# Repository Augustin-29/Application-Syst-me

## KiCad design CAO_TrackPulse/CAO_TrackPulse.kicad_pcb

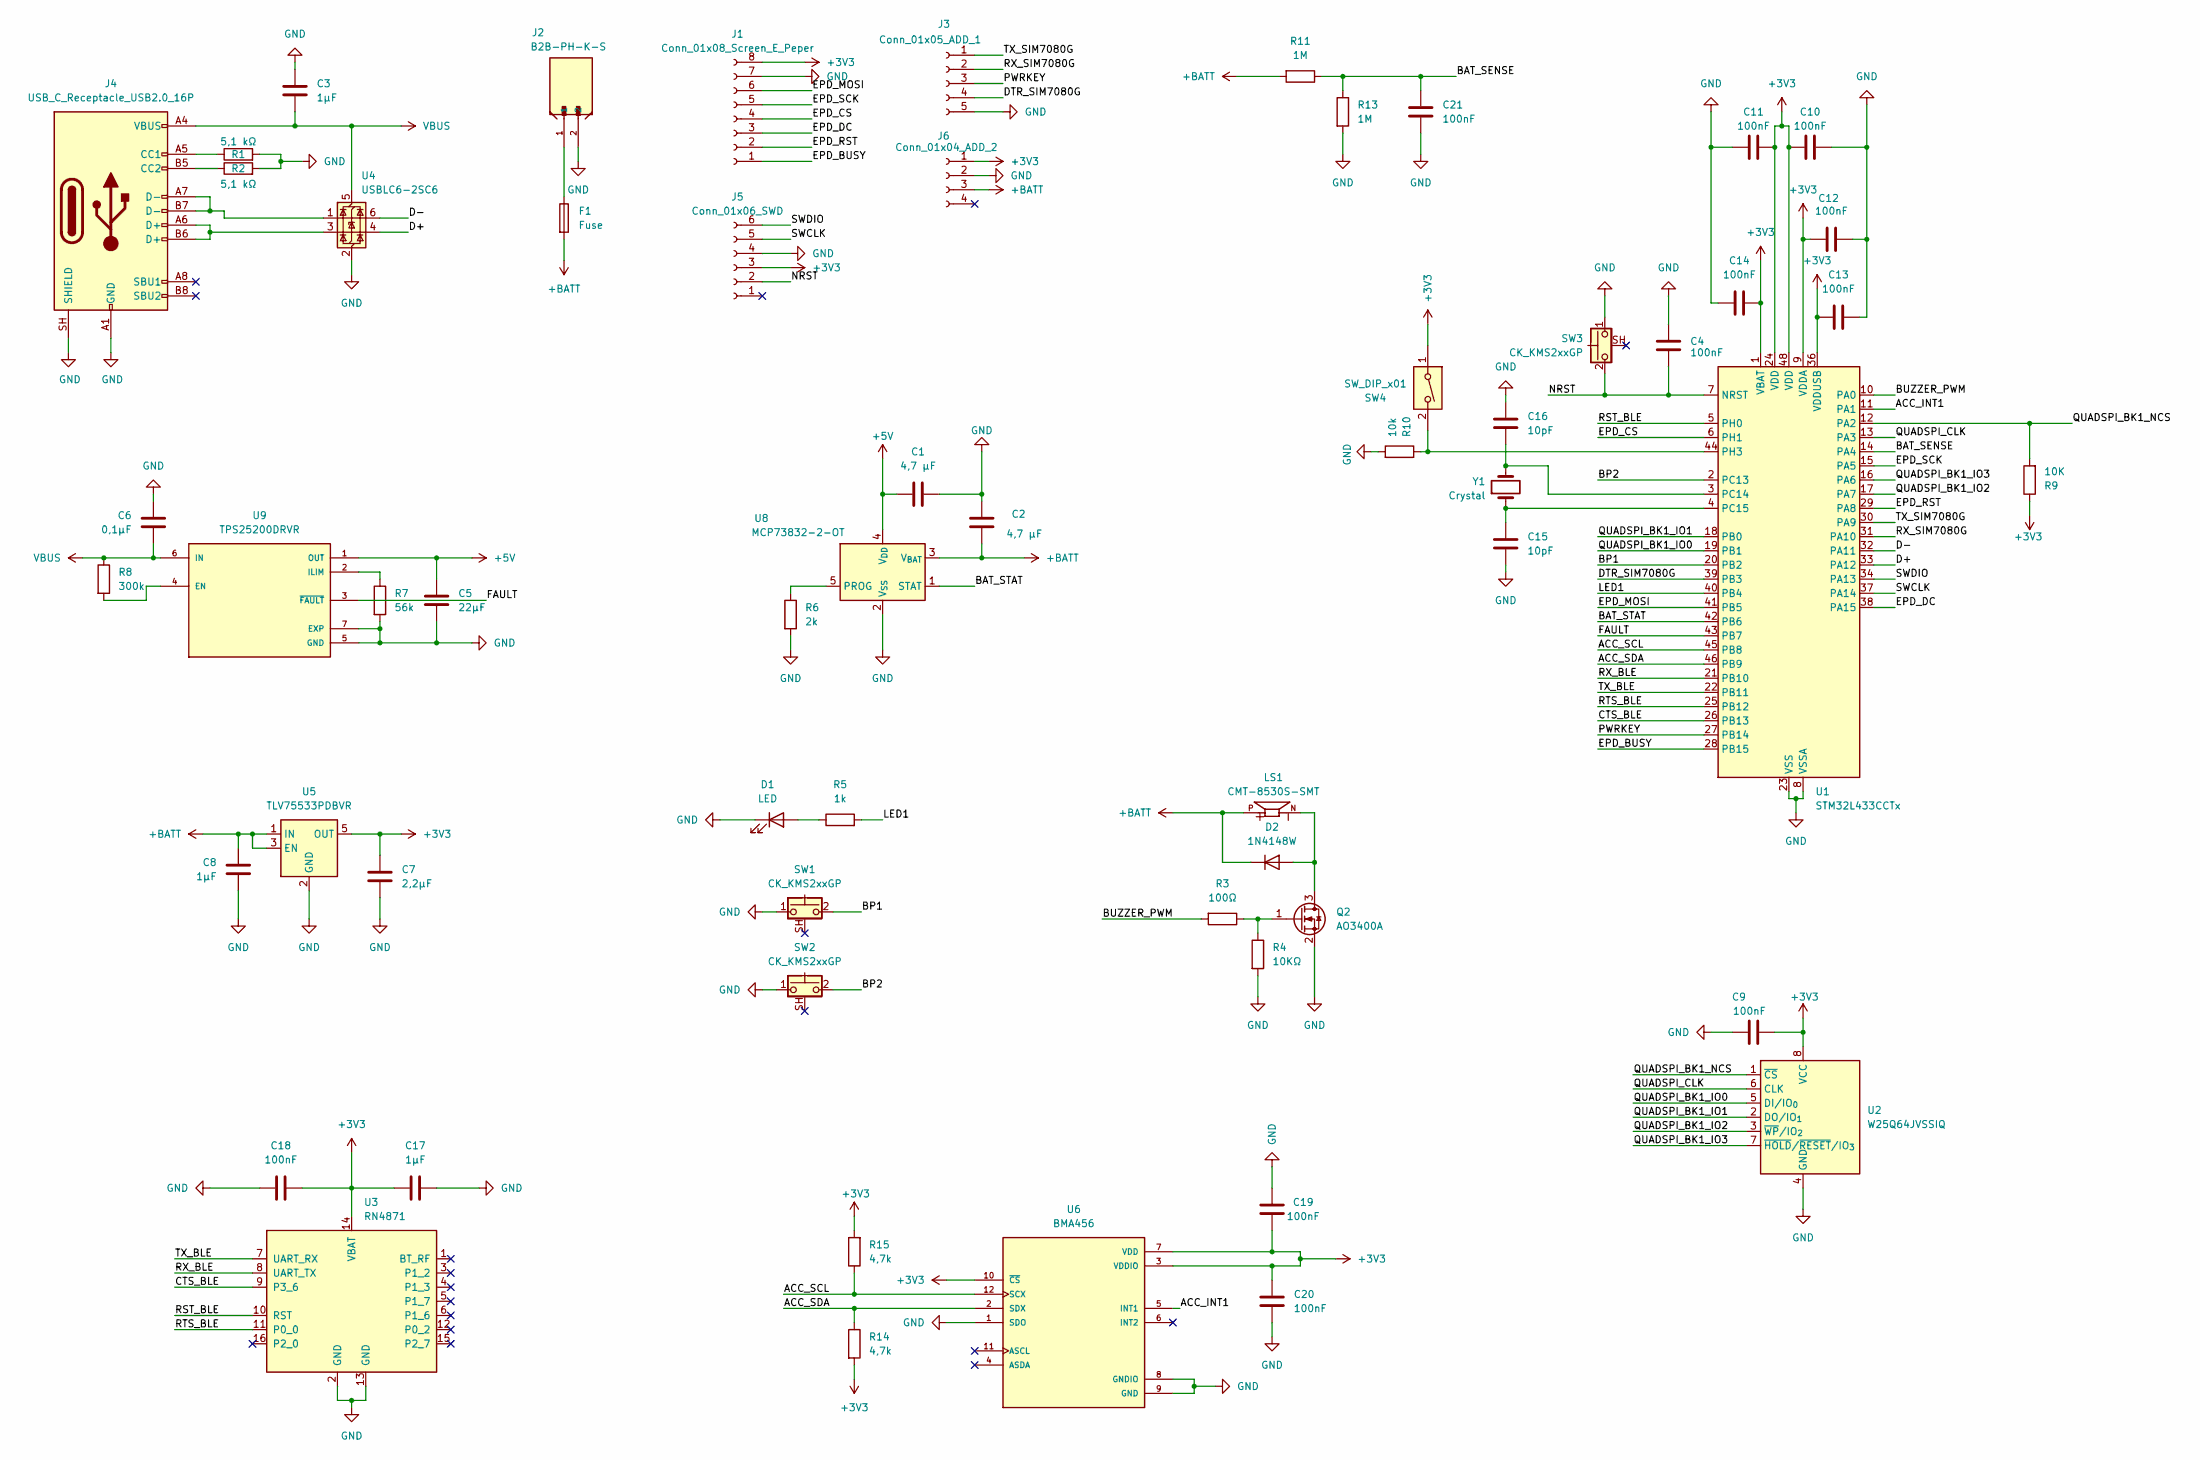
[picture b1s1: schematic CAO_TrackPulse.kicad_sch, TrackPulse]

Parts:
C1, C2: 4,7 µF; C_0805_2012Metric_Pad1.18x1.45mm_HandSolder
C3, C8, C17: 1µF; C_0805_2012Metric_Pad1.18x1.45mm_HandSolder
C4, C9, C10, C11, C12, C13, C14, C18, C19, C20, C21: 100nF; C_0805_2012Metric_Pad1.18x1.45mm_HandSolder
C5: 22µF; C_0805_2012Metric_Pad1.18x1.45mm_HandSolder
C6: 0,1µF; C_0805_2012Metric_Pad1.18x1.45mm_HandSolder
C7: 2,2µF; C_0805_2012Metric_Pad1.18x1.45mm_HandSolder
C15, C16: 10pF; C_0805_2012Metric_Pad1.18x1.45mm_HandSolder
D1: LED; LED_0805_2012Metric_Pad1.15x1.40mm_HandSolder
D2: 1N4148W; D_SOD-123
F1: Fuse; Fuse_0805_2012Metric_Pad1.15x1.40mm_HandSolder
J1: Conn_01x08_Screen_E_Peper; PinHeader_1x08_P2.54mm_Vertical
J2: B2B-PH-K-S; JST_B2B-PH-K-S
J3: Conn_01x05_ADD_1; PinHeader_1x05_P2.54mm_Vertical
J4: USB_C_Receptacle_USB2.0_16P; USB_C_Receptacle_HRO_TYPE-C-31-M-12
J5: Conn_01x06_SWD; Tag-Connect_TC2030-IDC-NL_2x03_P1.27mm_Vertical
J6: Conn_01x04_ADD_2; PinHeader_1x04_P2.54mm_Vertical
LS1: CMT-8530S-SMT; MagneticBuzzer_CUI_CMT-8504
Q2: AO3400A; SOT-23
R1, R2: 5,1 kΩ; C_0805_2012Metric_Pad1.18x1.45mm_HandSolder
R3: 100Ω; C_0805_2012Metric_Pad1.18x1.45mm_HandSolder
R4: 10KΩ; C_0805_2012Metric_Pad1.18x1.45mm_HandSolder
R5: 1k; C_0805_2012Metric_Pad1.18x1.45mm_HandSolder
R6: 2k; C_0805_2012Metric_Pad1.18x1.45mm_HandSolder
R7: 56k; C_0805_2012Metric_Pad1.18x1.45mm_HandSolder
R8: 300k; C_0805_2012Metric_Pad1.18x1.45mm_HandSolder
R9: 10K; C_0805_2012Metric_Pad1.18x1.45mm_HandSolder
R10: 10k; C_0805_2012Metric_Pad1.18x1.45mm_HandSolder
R11, R13: 1M; C_0805_2012Metric_Pad1.18x1.45mm_HandSolder
R14, R15: 4,7k; C_0805_2012Metric_Pad1.18x1.45mm_HandSolder
SW1, SW2, SW3: CK_KMS2xxGP; SW_SPST_CK_KMS2xxGP
SW4: SW_DIP_x01; SW_DIP_SPSTx01_Slide_Omron_A6S-110x_W8.9mm_P2.54mm
U1: STM32L433CCTx; LQFP-48_7x7mm_P0.5mm
U2: W25Q64JVSSIQ; SOIC-8_5.3x5.3mm_P1.27mm
U3: RN4871; Microchip_RN4871
U4: USBLC6-2SC6; SOT-23-6
U5: TLV75533PDBVR; SOT-23-5
U6: BMA456; LGA-12_2x2mm_P0.5mm; MPN BMA456
U8: MCP73832-2-OT; SOT-23-5
U9: TPS25200DRVR; WSON-6-1EP_2x2mm_P0.65mm_EP1x1.6mm; PARTREV D
Y1: Crystal; Crystal_SMD_3215-2Pin_3.2x1.5mm

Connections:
+3V3: C7.1, C9.2, C10.1, C11.1, C12.1, C13.1, C14.2, C17.1, C18.2, C19.1, C20.1, J1.8, J5.3, J6.1, R9.1, R14.2, R15.2, SW4.1, U1.1 (VBAT), U1.9 (VDDA), U1.24 (VDD), U1.36 (VDDUSB), U1.48 (VDD), U2.8 (VCC), U3.14 (VBAT), U5.5 (OUT), U6.3 (VDDIO), U6.7 (VDD), U6.10 (~CS)
+5V: C1.2, C5.1, U8.4 (V_{DD}), U9.1 (OUT)
+BATT: C2.1, C8.2, D2.1 (K), F1.2, J6.3, LS1.P, R11.2, U5.1 (IN), U5.3 (EN), U8.3 (V_{BAT})
/ACC_INT1: U1.11 (PA1), U6.5 (INT1)
/ACC_SCL: R15.1, U1.45 (PB8), U6.12 (SCX)
/ACC_SDA: R14.1, U1.46 (PB9), U6.2 (SDX)
/BAT_SENSE: C21.1, R11.1, R13.1, U1.14 (PA4)
/BAT_STAT: U1.42 (PB6), U8.1 (STAT)
/BP1: SW1.2, U1.20 (PB2)
/BP2: SW2.2, U1.2 (PC13)
/BUZZER_PWM: R3.2, U1.10 (PA0)
/CTS_BLE: U1.26 (PB13), U3.9 (P3_6)
/D+: U1.33 (PA12), U4.4 (I/O2)
/D-: U1.32 (PA11), U4.6 (I/O1)
/DTR_SIM7080G: J3.4, U1.39 (PB3)
/EPD_BUSY: J1.1, U1.28 (PB15)
/EPD_CS: J1.4, U1.6 (PH1)
/EPD_DC: J1.3, U1.38 (PA15)
/EPD_MOSI: J1.6, U1.41 (PB5)
/EPD_RST: J1.2, U1.29 (PA8)
/EPD_SCK: J1.5, U1.15 (PA5)
/FAULT: U1.43 (PB7), U9.3 (~FAULT)
/LED1: R5.2, U1.40 (PB4)
/NRST: C4.2, J5.2, SW3.2, U1.7 (NRST)
/PWRKEY: J3.3, U1.27 (PB14)
/QUADSPI_BK1_IO0: U1.19 (PB1), U2.5 (DI/IO_{0})
/QUADSPI_BK1_IO1: U1.18 (PB0), U2.2 (DO/IO_{1})
/QUADSPI_BK1_IO2: U1.17 (PA7), U2.3 (~WP/IO_{2})
/QUADSPI_BK1_IO3: U1.16 (PA6), U2.7 (~HOLD/~RESET/IO_{3})
/QUADSPI_BK1_NCS: R9.2, U1.12 (PA2), U2.1 (~CS)
/QUADSPI_CLK: U1.13 (PA3), U2.6 (CLK)
/RST_BLE: U1.5 (PH0), U3.10 (RST)
/RTS_BLE: U1.25 (PB12), U3.11 (P0_0)
/RX_BLE: U1.21 (PB10), U3.8 (UART_TX)
/RX_SIM7080G: J3.2, U1.31 (PA10)
/SWCLK: J5.5, U1.37 (PA14)
/SWDIO: J5.6, U1.34 (PA13)
/TX_BLE: U1.22 (PB11), U3.7 (UART_RX)
/TX_SIM7080G: J3.1, U1.30 (PA9)
GND: C1.1, C2.2, C3.1, C4.1, C5.2, C6.1, C7.2, C8.1, C9.1, C10.2, C11.2, C12.2, C13.2, C14.1, C15.2, C16.1, C17.2, C18.1, C19.2, C20.2, C21.2, D1.1 (K), J1.7, J2.2, J3.5, J4.A1 (GND), J4.A12 (GND), J4.B1 (GND), J4.B12 (GND), J4.SH (SHIELD), J5.4, J6.2, Q2.2 (S), R1.2, R2.2, R4.2, R6.2, R7.2, R10.2, R13.2, SW1.1, SW2.1, SW3.1, U1.8 (VSSA), U1.23 (VSS), U1.35 (VSS), U1.47 (VSS), U2.4 (GND), U3.2 (GND), U3.13 (GND), U4.2 (GND), U5.2 (GND), U6.1 (SDO), U6.8 (GNDIO), U6.9 (GND), U8.2 (V_{SS}), U9.5 (GND), U9.7 (EXP)
unnamed: D1.2 (A), R5.1
unnamed: D2.2 (A), LS1.N, Q2.3 (D)
unnamed: F1.1, J2.1
unnamed: J4.A5 (CC1), R1.1
unnamed: J4.B5 (CC2), R2.1
unnamed: J4.A6 (D+), J4.B6 (D+), U4.3 (I/O2)
unnamed: J4.A7 (D-), J4.B7 (D-), U4.1 (I/O1)
unnamed: Q2.1 (G), R3.1, R4.1
unnamed: C16.2, U1.3 (PC14), Y1.2
unnamed: C15.1, U1.4 (PC15), Y1.1
unnamed: R10.1, SW4.2, U1.44 (PH3)
unnamed: R6.1, U8.5 (PROG)
unnamed: R8.2, U9.4 (EN)
unnamed: R7.1, U9.2 (ILIM)
VBUS: C3.2, C6.2, J4.A4 (VBUS), J4.A9 (VBUS), J4.B4 (VBUS), J4.B9 (VBUS), R8.1, U4.5 (VBUS), U9.6 (IN)

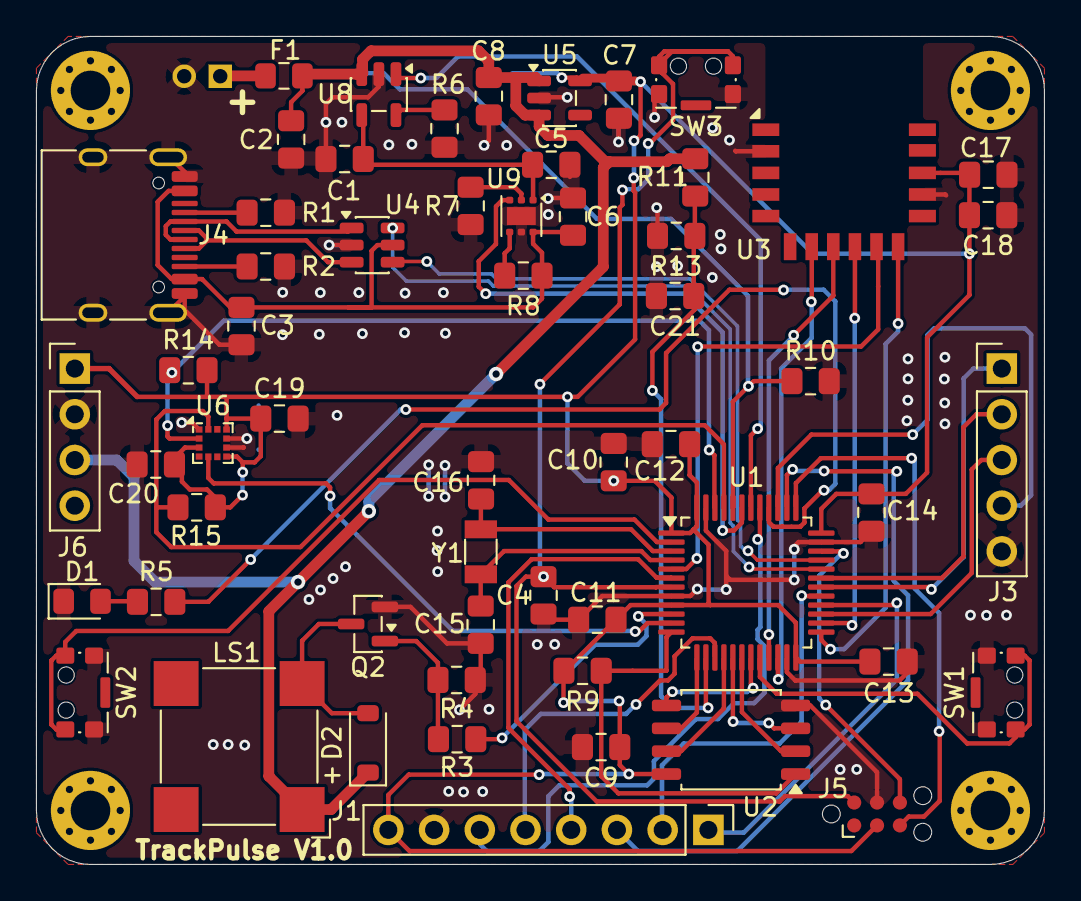
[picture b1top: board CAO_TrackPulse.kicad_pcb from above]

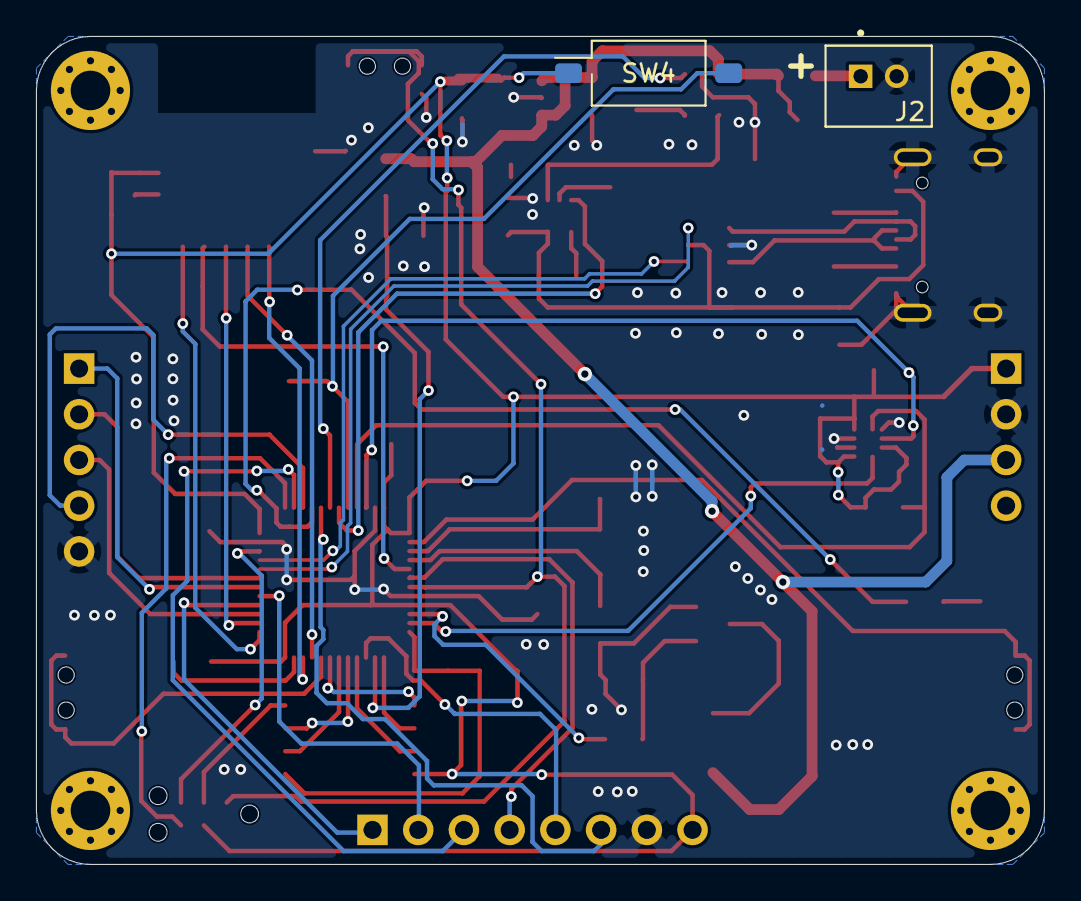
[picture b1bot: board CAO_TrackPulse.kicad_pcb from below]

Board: 2 copper layers, 56.0 x 46.0 mm, 59 parts (2 on the bottom side), 55 nets.

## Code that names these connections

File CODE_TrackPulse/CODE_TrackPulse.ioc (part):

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Mcu.Name=STM32L433C(B-C)Tx
Mcu.Package=LQFP48
Mcu.UserName=STM32L433CCTx
PA0.Signal=S_TIM2_CH1
PA1.GPIOParameters=GPIO_Label
PA1.GPIO_Label=ACC_INT1
PA1.Signal=GPXTI1
PA10.Mode=Asynchronous
PA10.Signal=USART1_RX
PA11.Mode=Device
PA11.Signal=USB_DM
PA12.Mode=Device
PA12.Signal=USB_DP
PA13\ (JTMS-SWDIO).Mode=Serial_Wire
PA13\ (JTMS-SWDIO).Signal=SYS_JTMS-SWDIO
PA14\ (JTCK-SWCLK).Mode=Serial_Wire
PA14\ (JTCK-SWCLK).Signal=SYS_JTCK-SWCLK
PA15\ (JTDI).GPIOParameters=GPIO_Label
PA15\ (JTDI).GPIO_Label=EPD_DC
PA15\ (JTDI).Signal=GPIO_Output
PA2.Mode=Single Bank 1
PA2.Signal=QUADSPI_BK1_NCS
PA3.Mode=Single Bank 1
PA3.Signal=QUADSPI_CLK
PA4.GPIOParameters=GPIO_Label
PA4.GPIO_Label=BAT_SENSE
PA4.Signal=ADCx_IN9
PA5.Mode=TX_Only_Simplex_Unidirect_Master
PA5.Signal=SPI1_SCK
PA6.Mode=Single Bank 1
PA6.Signal=QUADSPI_BK1_IO3
PA7.Mode=Single Bank 1
PA7.Signal=QUADSPI_BK1_IO2
PA8.GPIOParameters=PinState,GPIO_Label
PA8.GPIO_Label=EPD_RST
PA8.PinState=GPIO_PIN_SET
PA8.Signal=GPIO_Output
PA9.Mode=Asynchronous
PA9.Signal=USART1_TX
PB0.Mode=Single Bank 1
PB0.Signal=QUADSPI_BK1_IO1
PB1.Mode=Single Bank 1
PB1.Signal=QUADSPI_BK1_IO0
PB10.Mode=Asynchronous
PB10.Signal=LPUART1_RX
PB11.Mode=Asynchronous
PB11.Signal=LPUART1_TX
PB12.Mode=CTS_RTS
PB12.Signal=LPUART1_RTS
PB13.Mode=CTS_RTS
PB13.Signal=LPUART1_CTS
PB14.GPIOParameters=GPIO_Label
PB14.GPIO_Label=PWRKEY
PB14.Signal=GPIO_Output
PB15.GPIOParameters=GPIO_Label
PB15.GPIO_Label=EPD_BUSY
PB15.Signal=GPIO_Input
PB2.GPIOParameters=GPIO_PuPd,GPIO_Label
PB2.GPIO_Label=BP1
PB2.GPIO_PuPd=GPIO_PULLUP
PB2.Signal=GPIO_Input
PB3\ (JTDO-TRACESWO).GPIOParameters=GPIO_Label
PB3\ (JTDO-TRACESWO).GPIO_Label=DTR_SIM7080G
PB3\ (JTDO-TRACESWO).Signal=GPIO_Output
PB4\ (NJTRST).GPIOParameters=PinState,GPIO_Label
PB4\ (NJTRST).GPIO_Label=LED1
PB4\ (NJTRST).PinState=GPIO_PIN_SET
PB4\ (NJTRST).Signal=GPIO_Output
PB5.Mode=TX_Only_Simplex_Unidirect_Master
PB5.Signal=SPI1_MOSI
PB6.GPIOParameters=GPIO_PuPd,GPIO_Label
PB6.GPIO_Label=BAT_STAT
PB6.GPIO_PuPd=GPIO_PULLUP
PB6.Signal=GPIO_Input
PB7.GPIOParameters=GPIO_PuPd,GPIO_Label
PB7.GPIO_Label=FAULT
PB7.GPIO_PuPd=GPIO_PULLUP
PB7.Signal=GPIO_Input
PB8.Mode=I2C
PB8.Signal=I2C1_SCL
PB9.Mode=I2C
PB9.Signal=I2C1_SDA
PC13.GPIOParameters=GPIO_PuPd,GPIO_Label
PC13.GPIO_Label=BP2
PC13.GPIO_PuPd=GPIO_PULLUP
PC13.Signal=GPIO_Input
PC14-OSC32_IN\ (PC14).Mode=LSE-External-Oscillator
PC14-OSC32_IN\ (PC14).Signal=RCC_OSC32_IN
PC15-OSC32_OUT\ (PC15).Mode=LSE-External-Oscillator
PC15-OSC32_OUT\ (PC15).Signal=RCC_OSC32_OUT
PH0-OSC_IN\ (PH0).GPIOParameters=PinState,GPIO_Label
PH0-OSC_IN\ (PH0).GPIO_Label=RST_BLE
PH0-OSC_IN\ (PH0).PinState=GPIO_PIN_SET
PH0-OSC_IN\ (PH0).Signal=GPIO_Output
PH1-OSC_OUT\ (PH1).GPIOParameters=PinState,GPIO_Label
PH1-OSC_OUT\ (PH1).GPIO_Label=EPD_CS
PH1-OSC_OUT\ (PH1).PinState=GPIO_PIN_SET
PH1-OSC_OUT\ (PH1).Signal=GPIO_Output
RCC.HSE_VALUE=8000000
RCC.SYSCLKFreq_VALUE=80000000
RCC.SYSCLKSource=RCC_SYSCLKSOURCE_PLLCLK
board=custom
